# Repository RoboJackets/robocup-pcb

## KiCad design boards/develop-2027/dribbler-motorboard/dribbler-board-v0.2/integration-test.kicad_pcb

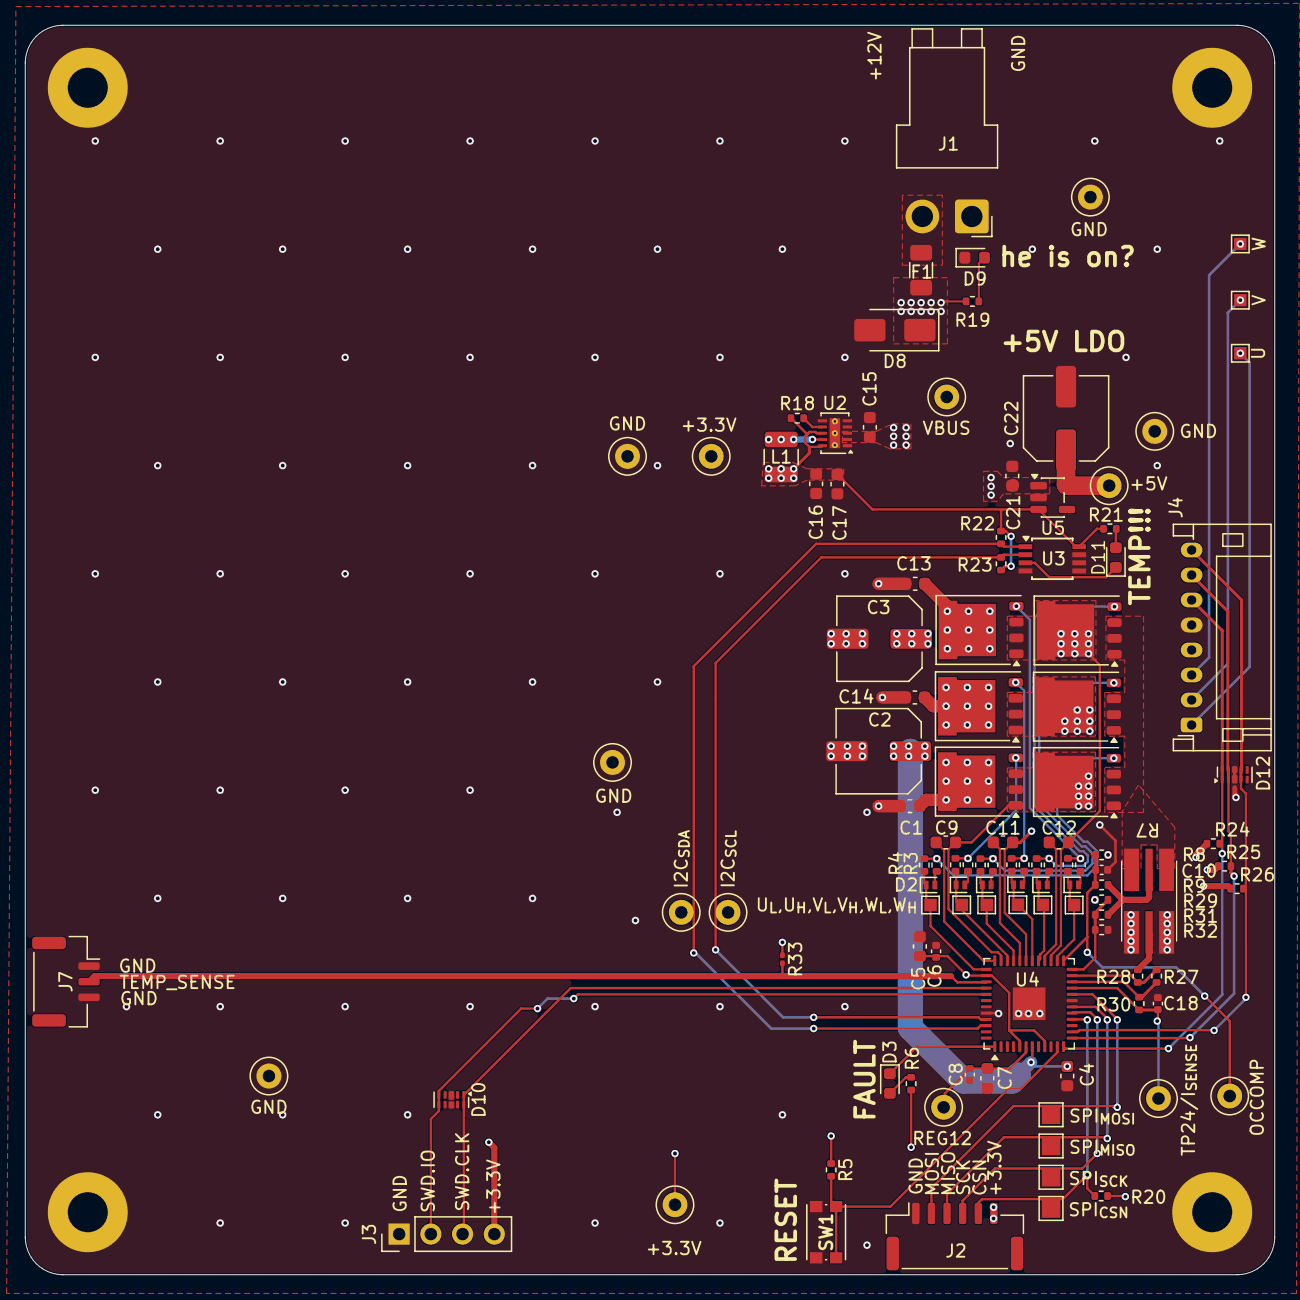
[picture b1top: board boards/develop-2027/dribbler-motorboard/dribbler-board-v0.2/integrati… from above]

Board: 4 copper layers, 100.0 x 100.0 mm, 114 parts (0 on the bottom side), 58 nets.

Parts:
+3.3V: 3.3V REG; TestPoint_Loop_D1.80mm_Drill1.0mm_Beaded
+3.3V#2: +5V EXT; TestPoint_Loop_D1.80mm_Drill1.0mm_Beaded
+5V: +5V; TestPoint_Loop_D1.80mm_Drill1.0mm_Beaded
C1, C4, C5, C9, C11, C12, C13, C14, C15, C21: 1u 63V; C_0603_1608Metric
C2, C3, C22: 100u 35V; C_Elec_6.3x5.8
C6, C8, C18: 100n 25V; C_0402_1005Metric
C7, C16, C17: 10u 25V; C_0603_1608Metric
C10: 33nF; C_0402_1005Metric
D1, D2, D4, D5, D6, D7: 1N4148WL2-TP; D_SOD-882
D3: FAULT; LED_0603_1608Metric
D8: SMAJ16A; D_SMA
D9: +12V; LED_0603_1608Metric
D10, D12: PUSB3FR4Z; Diodes_UDFN-10_1x2.5mm_P0.5mm
D11: OVERTEMP; LED_0603_1608Metric
F1: 12A; Fuse_1206_3216Metric
GND: GND; TestPoint_Loop_D1.80mm_Drill1.0mm_Beaded
GND#2, GND#4, GND#5: GND; TestPoint_Loop_D1.80mm_Drill1.0mm_Beaded
GND#3: GND EXT; TestPoint_Loop_D1.80mm_Drill1.0mm_Beaded
H1, H2, H3, H4: Corner; MountingHole_3.2mm_M3_Pad
I2C_{SCL}: SCL; TestPoint_Loop_D1.80mm_Drill1.0mm_Beaded
I2C_{SDA}: SDA; TestPoint_Loop_D1.80mm_Drill1.0mm_Beaded
J1: PWR_IN; JST_VH_B2PS-VH_1x02_P3.96mm_Horizontal
J2: COMM SPI; JST_GH_SM06B-GHS-TB_1x06-1MP_P1.25mm_Horizontal
J3: SWD Debug; PinHeader_1x04_P2.54mm_Vertical
J4: MOTOR PHASE; JST_PH_S8B-PH-K_1x08_P2.00mm_Horizontal
J7: Conn_01x03; JST_GH_SM03B-GHS-TB_1x03-1MP_P1.25mm_Horizontal
L1: 10u 540mA; L_1210_3225Metric
OCCOMP: OCCOMP; TestPoint_Loop_D1.80mm_Drill1.0mm_Beaded
Q1, Q2, Q3, Q4, Q5, Q6: STL90N10F7; PQFN-8-EP_6x5mm_P1.27mm_Generic
R1, R3, R10, R12, R14, R16: 0R; R_0402_1005Metric
R2, R4, R11, R13, R15, R17: 68R; R_0402_1005Metric
R5, R19, R20, R24, R25, R26: 10k; R_0402_1005Metric
R6, R21, R22, R23: 4.7k; R_0402_1005Metric
R7: 15m ±1% 3W; R_Shunt_Analog_2512_6332_HighAccuracy
R8: 1.13k ±0.1%; R_0402_1005Metric
R9: 33 ±0.1%; R_0402_1005Metric
R18: 100k; R_0402_1005Metric
R27: 120k ±0.1%; R_0402_1005Metric
R28, R31: 30k ±0.1%; R_0402_1005Metric
R29, R32: 240k ±0.1%; R_0402_1005Metric
R30: 300R ±1%; R_0402_1005Metric
R33: 10k; R_0201_0603Metric
REG12: REG12; TestPoint_Loop_D1.80mm_Drill1.0mm_Beaded
SPI_{CSN}: CSN; TestPoint_Pad_1.5x1.5mm
SPI_{MISO}: MISO; TestPoint_Pad_1.5x1.5mm
SPI_{MOSI}: MOSI; TestPoint_Pad_1.5x1.5mm
SPI_{SCK}: SCK; TestPoint_Pad_1.5x1.5mm
SW1: RESET; SW_Push_1P1T_NO_CK_KMR2
TP4: HSU; TestPoint_Pad_1.0x1.0mm
TP6: HSV; TestPoint_Pad_1.0x1.0mm
TP7: LSV; TestPoint_Pad_1.0x1.0mm
TP8: HSW; TestPoint_Pad_1.0x1.0mm
TP9: LSW; TestPoint_Pad_1.0x1.0mm
TP24/I_{SENSE}: ISENSEx; TestPoint_Loop_D1.80mm_Drill1.0mm_Beaded
U: OUT_{x}; TestPoint_Pad_1.0x1.0mm
U2: TPS62177DQC; WSON-10-1EP_2x3mm_P0.5mm_EP0.84x2.4mm_ThermalVias
U3: LM75ADP; TSSOP-8_3x3mm_P0.65mm
U4: STSPIN32G0B2; VQFN-48-1EP_7x7mm_P0.5mm_EP2.6x2.6mm
U5: LDI559-05EN; SOT-23-5
U_{L},U_{H},V_{L},V_{H},W_{L},W_{H}: LSU; TestPoint_Pad_1.0x1.0mm
V: OUT_{x}; TestPoint_Pad_1.0x1.0mm
VBUS: VBUS; TestPoint_Loop_D1.80mm_Drill1.0mm_Beaded
W: OUT_{x}; TestPoint_Pad_1.0x1.0mm

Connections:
+3.3V: +3.3V.1 (1_1), +3.3V#2.1 (1_1), C5.1, C6.1, C16.1, C17.1, J2.6, J3.4, L1.2, R5.1, R6.1, R8.2, R18.1, R20.1, R21.1, R22.1, R23.1, R24.1, R25.1, R26.1, R29.1, R33.1, U2.8 (~SLEEP), U2.10 (VOS), U3.8 (VCC), U4.5 (VDD), U4.9 (REG3V3), U4.38 (~STBY), U5.3 (EN)
+5V: +5V.1 (1_1), C22.1, J4.4 (+5V), U5.5 (VOUT)
/External Connections/SPI.CSN: J2.5, R20.2, SPI_{CSN}.1 (1_1), U4.16 (PA4/SPI1_~SS)
/External Connections/SPI.MISO: J2.3, SPI_{MISO}.1 (1_1), U4.18 (PA6/SPI1_MISO)
/External Connections/SPI.MOSI: J2.2, SPI_{MOSI}.1 (1_1), U4.20 (PA7/SPI1_MOSI)
/External Connections/SPI.SCK: J2.4, SPI_{SCK}.1 (1_1), U4.17 (PA5/SPI1_SCK)
/MOSFET Temperature Sensor/I2C.SCL: I2C_{SCL}.1 (1_1), R23.2, U3.2 (SCL), U4.45 (PB6/I2C1_SCL)
/MOSFET Temperature Sensor/I2C.SDA: I2C_{SDA}.1 (1_1), R22.2, U3.1 (SDA), U4.46 (PB7/I2C1_SDA)
/Motor Connections/HALL.A: D12.1 (CH1), D12.10 (CH1), J4.6 (HALL_A), R24.2, U4.12 (PA0/TIM2_CH1)
/Motor Connections/HALL.B: D12.2 (CH2), D12.9 (CH2), J4.7 (HALL_B), R25.2, U4.13 (PA1/TIM2_CH2)
/Motor Connections/HALL.C: D12.4 (CH3), D12.7 (CH3), J4.8 (HALL_C), R26.2, U4.14 (PA2/TIM2_CH3)
/Motor Connections/MOTORU: C9.2, J4.1 (PHASE_U), Q1.1 (S), Q1.2 (S), Q1.3 (S), Q2.5 (D), U.1 (1_1), U4.35 (OUTU)
/Motor Connections/MOTORV: C11.2, J4.2 (PHASE_V), Q3.1 (S), Q3.2 (S), Q3.3 (S), Q4.5 (D), U4.31 (OUTV), V.1 (1_1)
/Motor Connections/MOTORW: C12.2, J4.3 (PHASE_W), Q5.1 (S), Q5.2 (S), Q5.3 (S), Q6.5 (D), U4.27 (OUTW), W.1 (1_1)
/Motor Controller/Current Sensing/OPxN: R27.1, R28.2, U4.23 (OP1N)
/Motor Controller/Current Sensing/OPxO: R27.2, R30.1, U4.22 (OP1O)
/Motor Controller/Current Sensing/OPxP: R29.2, R31.2, R32.1, U4.24 (OP1P)
/Motor Controller/FAULT: D3.1 (K), U4.1 (PC13)
/Motor Controller/I_{SENSE}: C18.1, R30.2, TP24/I_{SENSE}.1 (1_1), U4.21 (PB1/ADC_IN)
/Motor Controller/Motor Phase U/HSx: D1.1 (K), R2.1, TP4.1 (1_1), U4.34 (HSU)
/Motor Controller/Motor Phase U/LSx: D2.1 (K), R4.1, U4.37 (LSU), U_{L},U_{H},V_{L},V_{H},W_{L},W_{H}.1 (1_1)
/Motor Controller/Motor Phase V/HSx: D4.1 (K), R11.1, TP6.1 (1_1), U4.30 (HSV)
/Motor Controller/Motor Phase V/LSx: D5.1 (K), R13.1, TP7.1 (1_1), U4.33 (LSV)
/Motor Controller/Motor Phase W/HSx: D6.1 (K), R15.1, TP8.1 (1_1), U4.26 (HSW)
/Motor Controller/Motor Phase W/LSx: D7.1 (K), R17.1, TP9.1 (1_1), U4.29 (LSW)
/Motor Controller/SHUNTN: R7.3, R28.1
/Motor Controller/SHUNTP: R7.2, R9.1, R31.1
/Motor Controller/SHUNT_H: Q2.1 (S), Q2.2 (S), Q2.3 (S), Q4.1 (S), Q4.2 (S), Q4.3 (S), Q6.1 (S), Q6.2 (S), Q6.3 (S), R7.1
/Motor Controller/SWD.CLK: D10.1 (CH1), D10.10 (CH1), J3.3, U4.40 (PA13/SWCLK)
/Motor Controller/SWD.IO: D10.5 (CH5), D10.6 (CH5), J3.2, U4.41 (PA14/SWDIO/BOOT0)
/Motor Controller/TEMP_SENSE: J7.2, R33.2, U4.39 (PA12[PA10]/SPI2_MOSI)
/Motor Controller/~RST: R5.2, SW1.2 (B), U4.11 (PF2/~RST)
GND: C1.2, C2.2, C3.2, C4.2, C5.2, C6.2, C7.2, C8.2, C10.2, C13.2, C14.2, C15.2, C16.2, C17.2, C18.2, C21.1, C22.2, D8.2 (A2), D9.1 (K), D10.3 (GND), D10.8 (GND), D12.3 (GND), D12.8 (GND), GND.1 (1_1), GND#2.1 (1_1), GND#3.1 (1_1), GND#4.1 (1_1), GND#5.1 (1_1), H1.1 (1_1), H2.1 (1_1), H3.1 (1_1), H4.1 (1_1), J1.1, J2.1, J3.1, J4.5 (GND), J7.1, J7.3, R7.4, R32.2, SW1.1 (A), U2.1 (PGND), U2.4 (NC), U2.5 (FB), U2.6 (AGND), U2.11 (PAD), U3.4 (GND), U3.5 (A2), U3.6 (A1), U3.7 (A0), U4.19 (TESTMODE), U4.44 (GND), U4.49 (EPAD), U5.2 (GND)
unnamed: D1.2 (A), R1.1
unnamed: D2.2 (A), R3.1
unnamed: D3.2 (A), R6.2
unnamed: D4.2 (A), R10.1
unnamed: D5.2 (A), R12.1
unnamed: D6.2 (A), R14.1
unnamed: D7.2 (A), R16.1
unnamed: D9.2 (A), R19.2
unnamed: D11.2 (A), R21.2
unnamed: D11.1 (K), U3.3 (OS)
unnamed: F1.1, J1.2
unnamed: Q1.4 (G), R1.2, R2.2
unnamed: Q2.4 (G), R3.2, R4.2
unnamed: Q3.4 (G), R10.2, R11.2
unnamed: Q4.4 (G), R12.2, R13.2
unnamed: Q5.4 (G), R14.2, R15.2
unnamed: Q6.4 (G), R16.2, R17.2
unnamed: R18.2, U2.7 (PG)
unnamed: L1.1, U2.9 (SW)
unnamed: C7.1, C8.1, REG12.1 (1_1), U4.6 (REG12)
unnamed: C9.1, U4.36 (VBOOTU)
unnamed: C11.1, U4.32 (VBOOTV)
unnamed: C12.1, U4.28 (VBOOTW)
unnamed: C10.1, OCCOMP.1 (1_1), R8.1, R9.2, U4.25 (OCCOMP)
VBUS: C1.1, C2.1, C3.1, C4.1, C13.1, C14.1, C15.1, C21.2, D8.1 (A1), F1.2, Q1.5 (D), Q3.5 (D), Q5.5 (D), R19.1, U2.2 (VIN), U2.3 (EN), U4.7 (VM), U5.1 (VIN), VBUS.1 (1_1)

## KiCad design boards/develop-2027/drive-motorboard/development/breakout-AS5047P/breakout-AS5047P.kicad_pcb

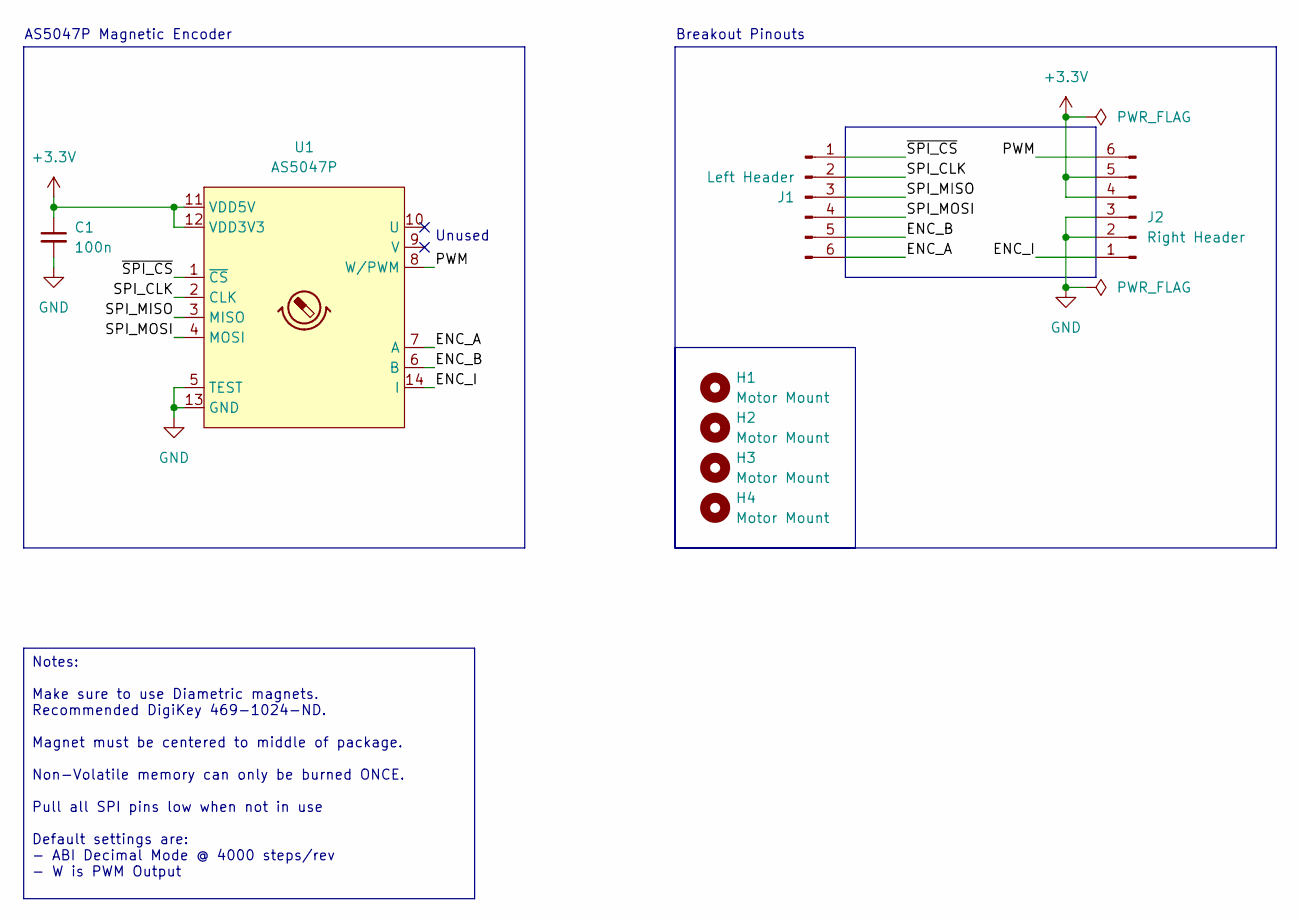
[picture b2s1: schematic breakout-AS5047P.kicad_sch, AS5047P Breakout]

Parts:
C1: 100n; C_0603_1608Metric_Pad1.08x0.95mm_HandSolder
H1, H2, H3, H4: Motor Mount; MountingHole_3.2mm_M3_Pad
J1: Left Header; PinHeader_1x06_P2.54mm_Vertical
J2: Right Header; PinHeader_1x06_P2.54mm_Vertical
U1: AS5047P; TSSOP-14_4.4x5mm_P0.65mm; Manufacturer P/N AS5047P

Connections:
+3.3V: C1.1, J2.4, J2.5, U1.11 (VDD5V), U1.12 (VDD3V3)
/ENC_A: J1.6, U1.7 (A)
/ENC_B: J1.5, U1.6 (B)
/ENC_I: J2.1, U1.14 (I)
/PWM: J2.6, U1.8 (W/PWM)
/SPI_CLK: J1.2, U1.2 (CLK)
/SPI_MISO: J1.3, U1.3 (MISO)
/SPI_MOSI: J1.4, U1.4 (MOSI)
/~SPI_CS: J1.1, U1.1 (~CS)
GND: C1.2, J2.2, J2.3, U1.5 (TEST), U1.13 (GND)

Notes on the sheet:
AS5047P Magnetic Encoder
Unused
Breakout Pinouts
Notes: Make sure to use Diametric magnets. Recommended DigiKey 469-1024-ND. Magnet must be centered to middle of package. Non-Volatile memory can only be burned ONCE. Pull all SPI pins low when not in use Default settings are: - ABI Decimal Mode @ 4000 steps/rev - W is PWM Output

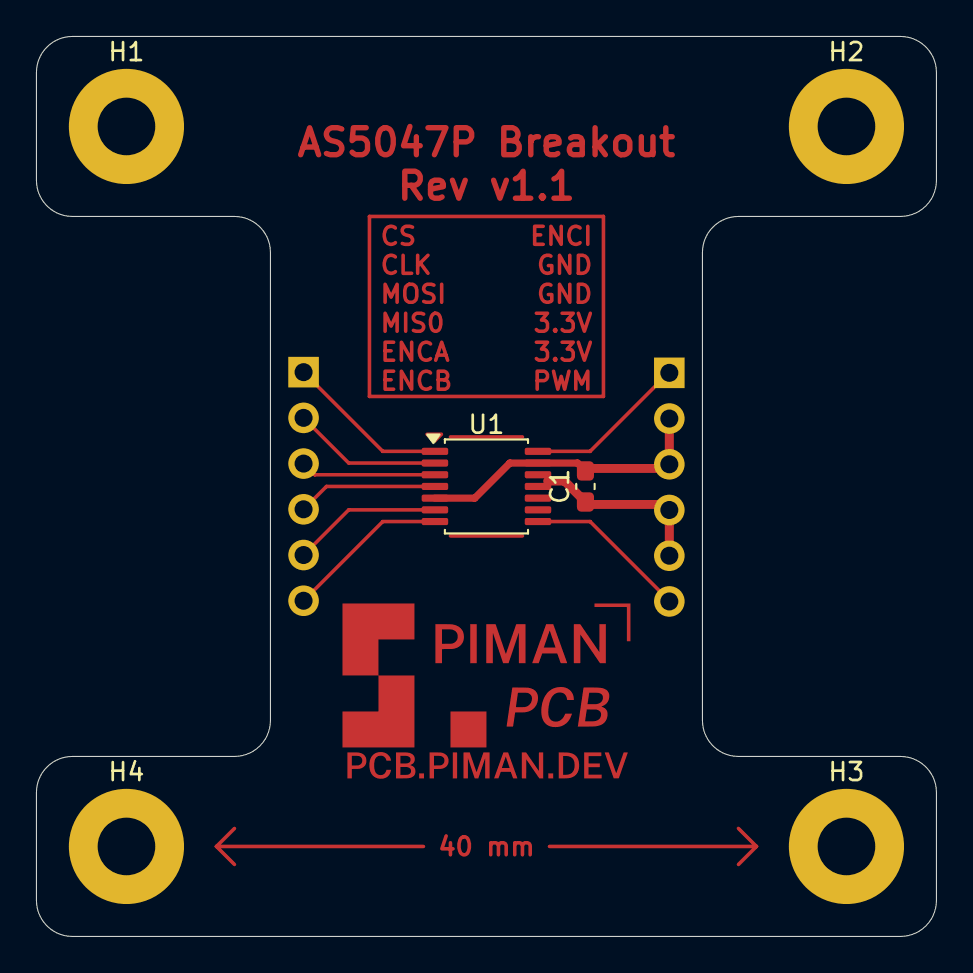
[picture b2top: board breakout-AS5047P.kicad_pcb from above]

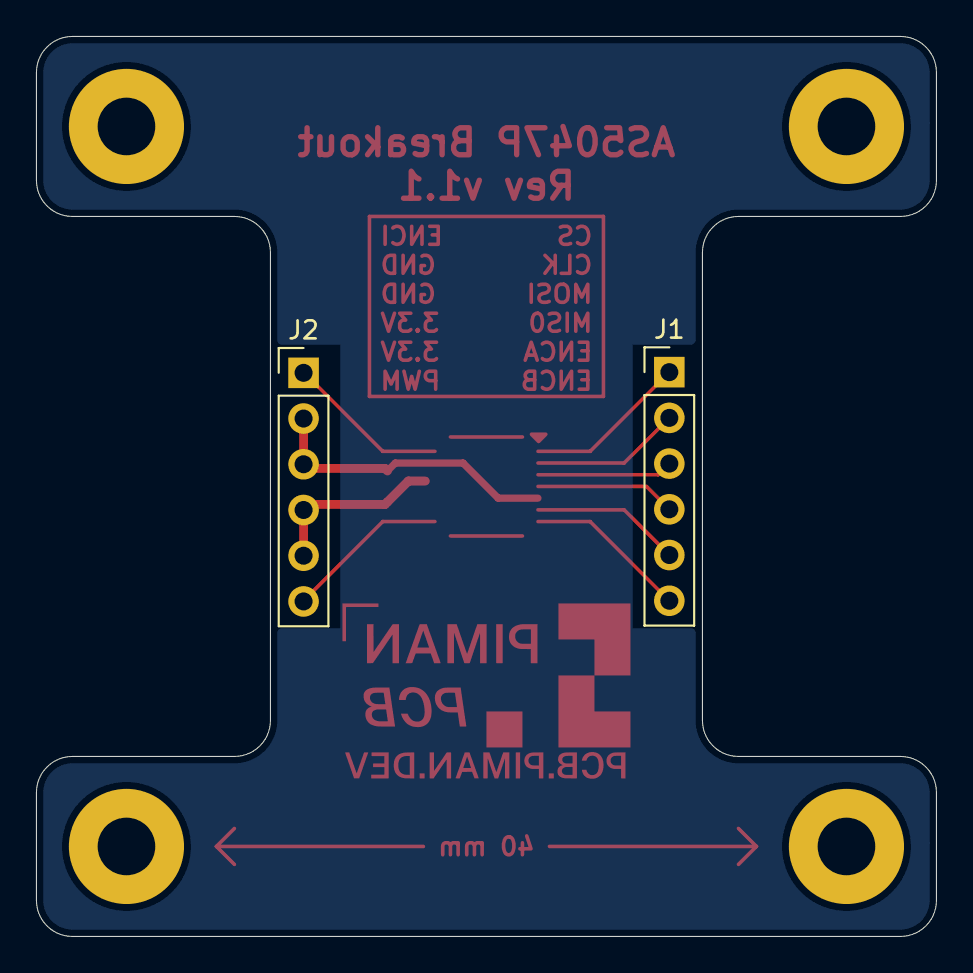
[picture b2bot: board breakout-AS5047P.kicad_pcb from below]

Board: 2 copper layers, 50.0 x 50.0 mm, 8 parts (2 on the bottom side), 10 nets.

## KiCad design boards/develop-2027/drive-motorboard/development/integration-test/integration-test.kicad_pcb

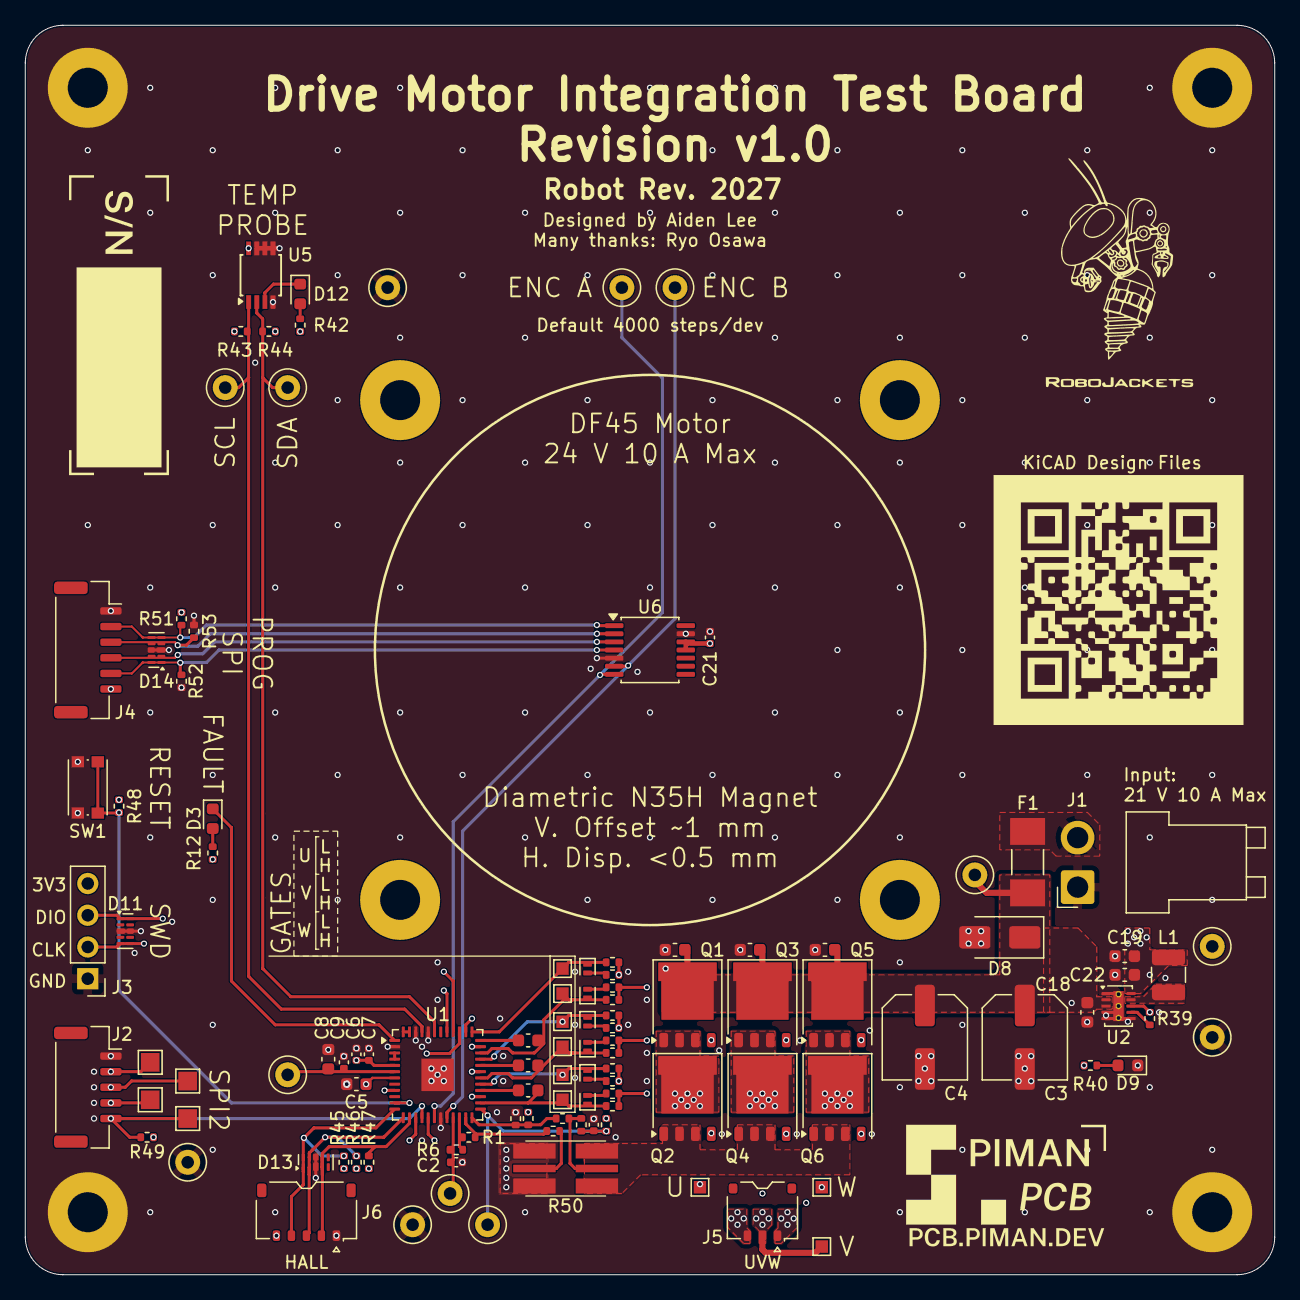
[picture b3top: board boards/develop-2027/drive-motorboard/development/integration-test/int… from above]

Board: 6 copper layers, 100.0 x 100.0 mm, 120 parts (0 on the bottom side), 64 nets.

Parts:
C1, C5, C10, C12, C13, C14, C15, C18: 1u 63V; C_0603_1608Metric
C2, C21: 100n; C_0402_1005Metric
C3, C4: 100u 35V; C_Elec_6.3x5.8
C6: 1u 10V; C_0402_1005Metric
C7: 100n 10V; C_0402_1005Metric
C8, C19, C22: 10u 25V; C_0603_1608Metric
C9: 100n 25V; C_0402_1005Metric
C11: 1n; C_0402_1005Metric
D1, D2, D4, D5, D6, D7: 1N4148WL2-TP; D_SOD-882
D3: FAULT; LED_0603_1608Metric
D8: SMAJ22A; D_SMA
D9: VBATT PWR; LED_0603_1608Metric
D11, D13, D14: PUSB3FR4Z; Diodes_UDFN-10_1x2.5mm_P0.5mm
D12: OVERTEMP; LED_0603_1608Metric
F1: 10A 60V; Fuse_2410_6125Metric
H1, H2, H3, H4: Corner; MountingHole_3.2mm_M3_Pad
H5, H6, H7, H8: Motor Mount; MountingHole_3.2mm_M3_Pad
J1: PWR_IN; JST_VH_B2PS-VH_1x02_P3.96mm_Horizontal
J2: COMM SPI; JST_GH_SM05B-GHS-TB_1x05-1MP_P1.25mm_Horizontal
J3: SWD Debug; PinHeader_1x04_P2.54mm_Vertical
J4: PROG SPI; JST_GH_SM06B-GHS-TB_1x06-1MP_P1.25mm_Horizontal
J5: MOTOR UVW; JST_ACH_BM03B-ACHSS-GAN-ETF_1x03-1MP_P1.20mm_Vertical
J6: MOTOR HALL; JST_ACH_BM05B-ACHSS-A-GAN-ETF_1x05-1MP_P1.20mm_Vertical
L1: 10u 540mA; L_1210_3225Metric
Q1, Q2, Q3, Q4, Q5, Q6: STL90N10F7; PQFN-8-EP_6x5mm_P1.27mm_Generic
R1: 8.25k ±0.1%; R_0402_1005Metric
R2, R8, R18, R19, R22, R23: 0R; R_0402_1005Metric
R3, R7, R15: 1.13k ±0.1%; R_0402_1005Metric
R4, R10, R11, R17, R20, R21: 68R; R_0402_1005Metric
R5, R9: 16.5k ±0.1%; R_0402_1005Metric
R6: 300R ±1%; R_0402_1005Metric
R12, R42, R43, R44, R51, R52, R53: 4.7k; R_0402_1005Metric
R14: 33k ±0.1%; R_0402_1005Metric
R39: 100k; R_0402_1005Metric
R40, R45, R46, R47, R48, R49: 10k; R_0402_1005Metric
R50: 15m ±1% 3W; R_Shunt_Analog_2512_6332_HighAccuracy
SW1: RESET; SW_Push_1P1T_NO_CK_KMR2
TP1: ISENSEx; TestPoint_Loop_D1.80mm_Drill1.0mm_Beaded
TP6: REG12; TestPoint_Loop_D1.80mm_Drill1.0mm_Beaded
TP7: OCCOMP; TestPoint_Loop_D1.80mm_Drill1.0mm_Beaded
TP8: HSU; TestPoint_Pad_1.0x1.0mm
TP9: LSU; TestPoint_Pad_1.0x1.0mm
TP10: HSV; TestPoint_Pad_1.0x1.0mm
TP11: LSV; TestPoint_Pad_1.0x1.0mm
TP12: HSW; TestPoint_Pad_1.0x1.0mm
TP13: LSW; TestPoint_Pad_1.0x1.0mm
TP14, TP15, TP16: OUT_{x}; TestPoint_Pad_1.0x1.0mm
TP20: 3.3V REG; TestPoint_Loop_D1.80mm_Drill1.0mm_Beaded
TP21: VBUS; TestPoint_Loop_D1.80mm_Drill1.0mm_Beaded
TP22, TP23, TP24, TP25: GND; TestPoint_Loop_D1.80mm_Drill1.0mm_Beaded
TP27: CSN; TestPoint_Pad_1.5x1.5mm
TP28: SCK; TestPoint_Pad_1.5x1.5mm
TP29: MISO; TestPoint_Pad_1.5x1.5mm
TP30: MOSI; TestPoint_Pad_1.5x1.5mm
TP31: SDA; TestPoint_Loop_D1.80mm_Drill1.0mm_Beaded
TP32: SCL; TestPoint_Loop_D1.80mm_Drill1.0mm_Beaded
TP33: ENC A; TestPoint_Loop_D1.80mm_Drill1.0mm_Beaded
TP34: ENC B; TestPoint_Loop_D1.80mm_Drill1.0mm_Beaded
U1: STSPIN32G0A2; VQFN-48-1EP_7x7mm_P0.5mm_EP2.6x2.6mm
U2: TPS62177DQC; WSON-10-1EP_2x3mm_P0.5mm_EP0.84x2.4mm_ThermalVias
U5: LM75ADP; TSSOP-8_3x3mm_P0.65mm
U6: AS5047P; TSSOP-14_4.4x5mm_P0.65mm

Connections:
+3.3V: C6.1, C7.1, C19.1, C21.1, C22.1, J3.4, J4.6, J6.5, L1.2, R5.1, R12.1, R14.2, R39.1, R42.1, R43.1, R44.1, R45.1, R46.1, R47.1, R48.1, R49.1, R51.1, TP20.1 (1_1), U1.5 (VDD), U1.9 (REG3V3), U1.38 (~STBY), U2.8 (~SLEEP), U2.10 (VOS), U5.8 (VCC), U6.11 (VDD5V), U6.12 (VDD3V3)
/External Connections/SPI.CSN: J2.5, R49.2, TP27.1 (1_1), U1.16 (PA4/SPI2_~SS)
/External Connections/SPI.MISO: J2.3, TP29.1 (1_1), U1.15 (PA3/SPI2_MISO)
/External Connections/SPI.MOSI: J2.2, TP30.1 (1_1), U1.39 (PA12[PA10]/SPI2_MOSI)
/External Connections/SPI.SCK: J2.4, TP28.1 (1_1), U1.17 (PA5/SPI2_SCK)
/Magnetic Encoder/ENC.A: TP33.1 (1_1), U1.18 (PA6/TIM3_CH1), U6.7 (A)
/Magnetic Encoder/ENC.B: TP34.1 (1_1), U1.20 (PA7/TIM3_CH2), U6.6 (B)
/Magnetic Encoder/PROGSPI.CLK: D14.4 (CH3), D14.7 (CH3), J4.3, R53.1, U6.2 (CLK)
/Magnetic Encoder/PROGSPI.CSN: D14.5 (CH5), D14.6 (CH5), J4.2, R51.2, U6.1 (~CS)
/Magnetic Encoder/PROGSPI.MISO: D14.2 (CH2), D14.9 (CH2), J4.4, U6.3 (MISO)
/Magnetic Encoder/PROGSPI.MOSI: D14.1 (CH1), D14.10 (CH1), J4.5, R52.1, U6.4 (MOSI)
/Motor Connections/HALL.A: D13.1 (CH1), D13.10 (CH1), J6.4, R45.2, U1.12 (PA0/TIM2_CH1)
/Motor Connections/HALL.B: D13.2 (CH2), D13.9 (CH2), J6.3, R46.2, U1.13 (PA1/TIM2_CH2)
/Motor Connections/HALL.C: D13.4 (CH3), D13.7 (CH3), J6.2, R47.2, U1.14 (PA2/TIM2_CH3)
/Motor Connections/MOTORU: J5.3, Q1.1 (S), Q1.2 (S), Q1.3 (S), Q2.5 (D), TP14.1 (1_1), U1.35 (OUTU)
/Motor Connections/MOTORV: J5.2, Q3.1 (S), Q3.2 (S), Q3.3 (S), Q4.5 (D), TP15.1 (1_1), U1.31 (OUTV)
/Motor Connections/MOTORW: J5.1, Q5.1 (S), Q5.2 (S), Q5.3 (S), Q6.5 (D), TP16.1 (1_1), U1.27 (OUTW)
/Motor Controller/Current Sensing/OPxN: R1.1, R3.2, U1.23 (OP1N)
/Motor Controller/Current Sensing/OPxO: R1.2, R6.1, U1.22 (OP1O)
/Motor Controller/Current Sensing/OPxP: R5.2, R7.2, R9.1, U1.24 (OP1P)
/Motor Controller/FAULT: D3.1 (K), U1.1 (PC14)
/Motor Controller/I2C.SCL: R44.2, TP32.1 (1_1), U1.43 (PB6/I2C1_SCL), U5.2 (SCL)
/Motor Controller/I2C.SDA: R43.2, TP31.1 (1_1), U1.45 (PB7/I2C1_SDA), U5.1 (SDA)
/Motor Controller/I_{SENSE}: C2.1, R6.2, TP1.1 (1_1), U1.21 (PB1)
/Motor Controller/Motor Phase U/HSx: C10.2, D1.1 (K), R4.1, TP8.1 (1_1), U1.34 (HSU)
/Motor Controller/Motor Phase U/LSx: D2.1 (K), R10.1, TP9.1 (1_1), U1.37 (LSU)
/Motor Controller/Motor Phase V/HSx: C12.2, D4.1 (K), R11.1, TP10.1 (1_1), U1.30 (HSV)
/Motor Controller/Motor Phase V/LSx: D5.1 (K), R17.1, TP11.1 (1_1), U1.33 (LSV)
/Motor Controller/Motor Phase W/HSx: C13.2, D6.1 (K), R20.1, TP12.1 (1_1), U1.26 (HSW)
/Motor Controller/Motor Phase W/LSx: D7.1 (K), R21.1, TP13.1 (1_1), U1.29 (LSW)
/Motor Controller/SHUNTN: R3.1, R50.3
/Motor Controller/SHUNTP: R7.1, R15.1, R50.2
/Motor Controller/SHUNT_H: Q2.1 (S), Q2.2 (S), Q2.3 (S), Q4.1 (S), Q4.2 (S), Q4.3 (S), Q6.1 (S), Q6.2 (S), Q6.3 (S), R50.1
/Motor Controller/SWD.CLK: D11.5 (CH5), D11.6 (CH5), J3.2, U1.41 (PA14/SWDCLK/BOOT0)
/Motor Controller/SWD.IO: D11.1 (CH1), D11.10 (CH1), J3.3, U1.40 (PA13/SWDIO)
/Motor Controller/~RST: R48.2, SW1.2 (B), U1.11 (PF2/~RST)
GND: C1.2, C2.2, C3.2, C4.2, C5.2, C6.2, C7.2, C8.2, C9.2, C11.2, C14.2, C15.2, C18.2, C19.2, C21.2, C22.2, D8.2 (A2), D9.1 (K), D11.3 (GND), D11.8 (GND), D13.3 (GND), D13.8 (GND), D14.3 (GND), D14.8 (GND), H1.1 (1_1), H2.1 (1_1), H3.1 (1_1), H4.1 (1_1), J1.1, J2.1, J3.1, J4.1, J6.1, R9.2, R50.4, R52.2, R53.2, SW1.1 (A), TP22.1 (1_1), TP23.1 (1_1), TP24.1 (1_1), TP25.1 (1_1), U1.2 (OP2P), U1.19 (TESTMODE), U1.44 (GND), U1.46 (OP3P), U1.49 (EPAD), U2.1 (PGND), U2.4 (NC), U2.5 (FB), U2.6 (AGND), U2.11 (PAD), U5.4 (GND), U5.5 (A2), U5.6 (A1), U5.7 (A0), U6.5 (TEST), U6.13 (GND)
unnamed: D1.2 (A), R2.1
unnamed: D2.2 (A), R8.1
unnamed: D3.2 (A), R12.2
unnamed: D4.2 (A), R18.1
unnamed: D5.2 (A), R19.1
unnamed: D6.2 (A), R22.1
unnamed: D7.2 (A), R23.1
unnamed: D9.2 (A), R40.2
unnamed: D12.2 (A), R42.2
unnamed: D12.1 (K), U5.3 (OS)
unnamed: F1.1, J1.2
unnamed: Q1.4 (G), R2.2, R4.2
unnamed: Q2.4 (G), R8.2, R10.2
unnamed: Q3.4 (G), R11.2, R18.2
unnamed: Q4.4 (G), R17.2, R19.2
unnamed: Q5.4 (G), R20.2, R22.2
unnamed: Q6.4 (G), R21.2, R23.2
unnamed: C10.1, U1.36 (VBOOTU)
unnamed: C12.1, U1.32 (VBOOTV)
unnamed: C13.1, U1.28 (VBOOTW)
unnamed: U1.3 (OP2N), U1.4 (OP2O)
unnamed: U1.47 (OP3N), U1.48 (OP3O)
unnamed: C11.1, R14.1, R15.2, TP7.1 (1_1), U1.25 (OCCOMP)
unnamed: C8.1, C9.1, TP6.1 (1_1), U1.6 (REG12)
unnamed: R39.2, U2.7 (PG)
unnamed: L1.1, U2.9 (SW)
VBUS: C1.1, C3.1, C4.1, C5.1, C14.1, C15.1, C18.1, D8.1 (A1), F1.2, Q1.5 (D), Q3.5 (D), Q5.5 (D), R40.1, TP21.1 (1_1), U1.7 (VM), U2.2 (VIN), U2.3 (EN)

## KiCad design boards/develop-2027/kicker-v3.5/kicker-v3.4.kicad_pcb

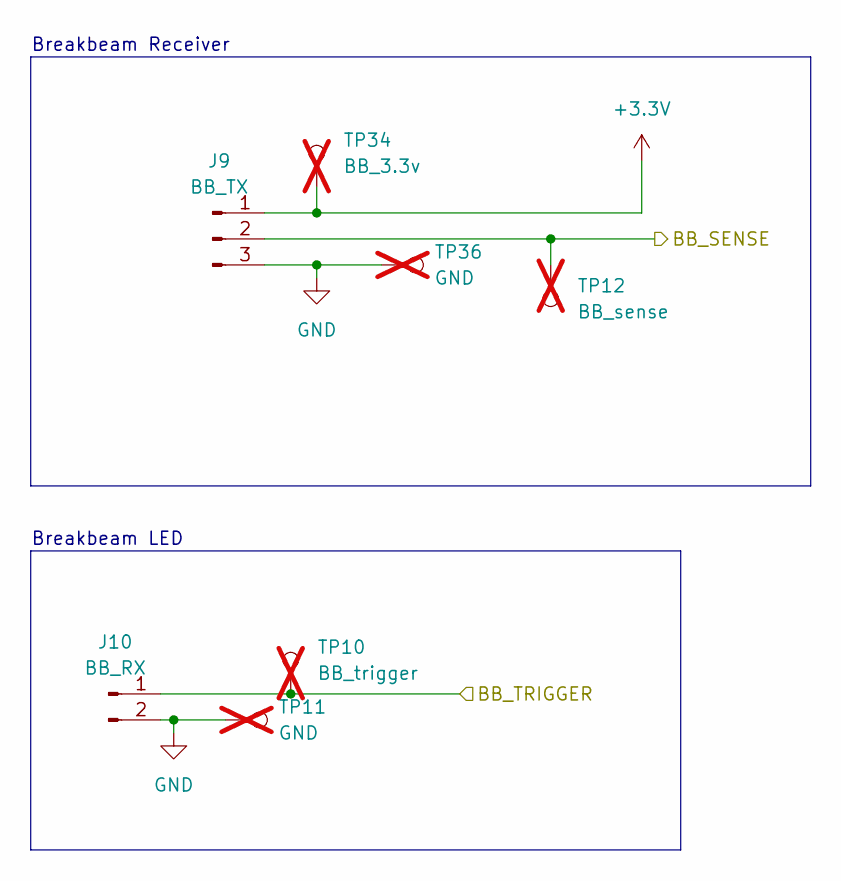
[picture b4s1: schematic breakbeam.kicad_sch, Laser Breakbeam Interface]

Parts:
J9: BB_TX; JST_PH_S3B-PH-K_1x03_P2.00mm_Horizontal; Manufacturer P/N IPCW200W13NW01R; LCSC P/N C2982156
J10: BB_RX; JST_PH_S2B-PH-K_1x02_P2.00mm_Horizontal; Manufacturer P/N IPCW200W12NW01R; LCSC P/N C2982155
TP10: BB_trigger; TestPoint_Pad_D1.0mm; not fitted
TP11, TP36: GND; TestPoint_Pad_D1.0mm; not fitted
TP12: BB_sense; TestPoint_Pad_D1.0mm; not fitted
TP34: BB_3.3v; TestPoint_Pad_D1.0mm; not fitted

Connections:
+3.3V: J9.1, TP34.1 (1_1); also elsewhere on the board
/Breakbeam/BB_SENSE: J9.2, TP12.1 (1_1); also elsewhere on the board
/Breakbeam/BB_TRIGGER: J10.1, TP10.1 (1_1); also elsewhere on the board
GND: J9.3, J10.2, TP11.1 (1_1), TP36.1 (1_1); also elsewhere on the board

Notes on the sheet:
Breakbeam LED
Breakbeam Receiver

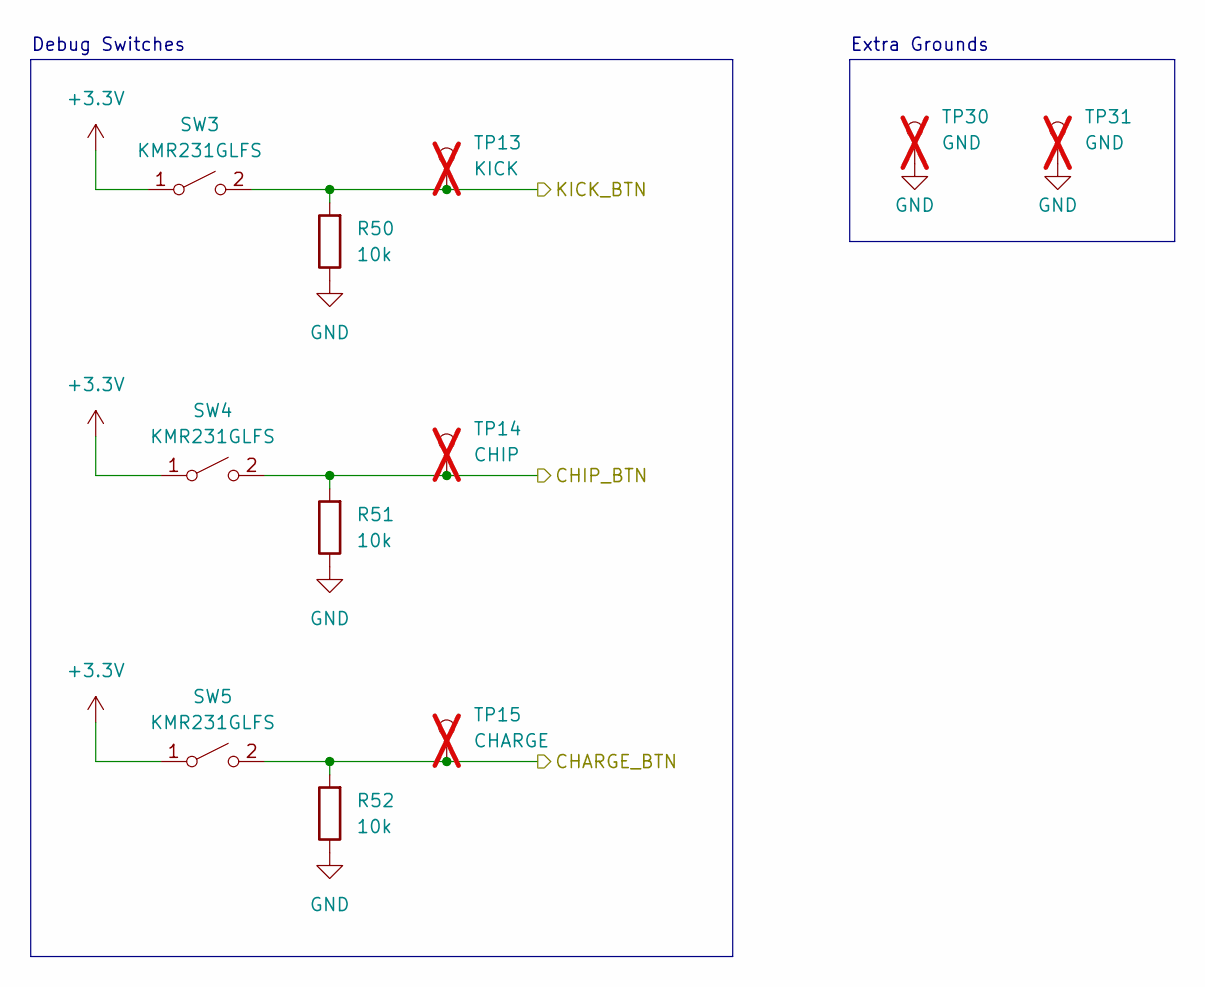
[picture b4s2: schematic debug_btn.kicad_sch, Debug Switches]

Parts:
R50, R51, R52: 10k; R_0603_1608Metric; Manufacturer P/N RC0603FR-0710KL; LCSC P/N C98220
SW3, SW4, SW5: KMR231GLFS; SW_Push_1P1T_NO_CK_KMR2; Manufacturer P/N KMR231GLFS
TP13: KICK; TestPoint_Pad_D1.0mm; not fitted
TP14: CHIP; TestPoint_Pad_D1.0mm; not fitted
TP15: CHARGE; TestPoint_Pad_D1.0mm; not fitted
TP30, TP31: GND; TestPoint_Pad_D1.0mm; not fitted

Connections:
+3.3V: SW3.1 (A), SW4.1 (A), SW5.1 (A); also elsewhere on the board
/Debug Buttons/CHARGE_BTN: R52.2, SW5.2 (B), TP15.1 (1_1); also elsewhere on the board
/Debug Buttons/CHIP_BTN: R51.2, SW4.2 (B), TP14.1 (1_1); also elsewhere on the board
/Debug Buttons/KICK_BTN: R50.2, SW3.2 (B), TP13.1 (1_1); also elsewhere on the board
GND: R50.1, R51.1, R52.1, TP30.1 (1_1), TP31.1 (1_1); also elsewhere on the board

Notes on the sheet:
Extra Grounds
Debug Switches

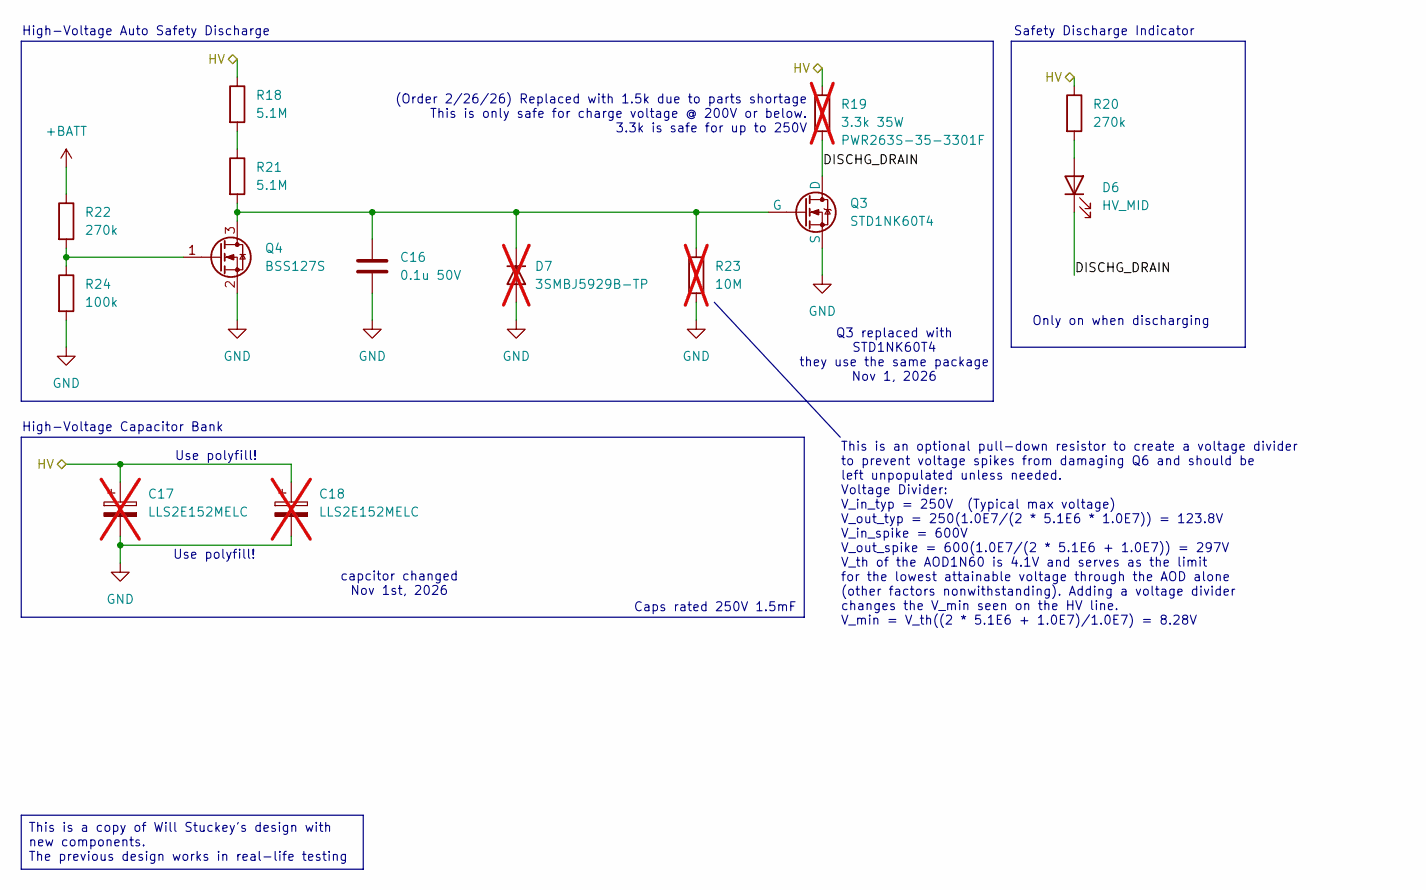
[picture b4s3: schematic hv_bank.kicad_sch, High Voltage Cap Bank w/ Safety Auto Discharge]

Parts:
C16: 0.1u 50V; C_0603_1608Metric; Manufacturer P/N CL10B104KB8NNNC; LCSC P/N C1591
C17, C18: LLS2E152MELC; CAP_C40_NCH; not fitted
D6: HV_MID; LED_0603_1608Metric; LCSC P/N C965804
D7: 3SMBJ5929B-TP; D_SMB; Manufacturer P/N 3SMBJ5929B-TP; not fitted
Q3: STD1NK60T4; TO-252-2; Manufacturer P/N STD1NK60T4; LCSC P/N C361030
Q4: BSS127S; SOT-23; Manufacturer P/N BSS127S; LCSC P/N C154890
R18, R21: 5.1M; R_1206_3216Metric; Manufacturer P/N RCT065M1FLF; LCSC P/N C185741
R19: 3.3k 35W; RES_PWR263S-35-3301F; Manufacturer P/N PWR263S-35-3301F; not fitted
R20: 270k; R_2512_6332Metric; Manufacturer P/N HP122WF2703T4E; LCSC P/N C2775917
R22: 270k; R_0603_1608Metric; Manufacturer P/N RC0603FR-07270KL; LCSC P/N C137755
R23: 10M; R_0603_1608Metric; not fitted
R24: 100k; R_0603_1608Metric; Manufacturer P/N RC0603FR-07100KL; LCSC P/N C14675

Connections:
+BATT: R22.1; also elsewhere on the board
/Capacitor Bank/DISCHG_DRAIN: D6.1 (K), Q3.2 (D), R19.2
/Capacitor Bank/HV: C17.1, C18.1, R18.1, R19.1, R20.1; also elsewhere on the board
GND: C16.2, C17.2, C18.2, D7.2 (A), Q3.3 (S), Q4.2 (S), R23.2, R24.2; also elsewhere on the board
unnamed: D6.2 (A), R20.2
unnamed: C16.1, D7.1 (K), Q3.1 (G), Q4.3 (D), R21.2, R23.1
unnamed: Q4.1 (G), R22.2, R24.1
unnamed: R18.2, R21.1

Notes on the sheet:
Safety Discharge Indicator
capcitor changed Nov 1st, 2026
Only on when discharging
High-Voltage Capacitor Bank
Use polyfill!
Caps rated 250V 1.5mF
High-Voltage Auto Safety Discharge
(Order 2/26/26) Replaced with 1.5k due to parts shortage This is only safe for charge voltage @ 200V or below. 3.3k is safe for up to 250V
Q3 replaced with STD1NK60T4 they use the same package Nov 1, 2026
This is an optional pull-down resistor to create a voltage divider to prevent voltage spikes from damaging Q6 and should be left unpopulated unless needed. Voltage Divider: V_in_typ = 250V (Typical max voltage) V_out_typ = 250(1.0E7/(2 * 5.1E6 * 1.0E7)) = 123.8V V_in_spike = 600V V_out_spike = 600(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
This is a copy of Will Stuckey's design with new components. The previous design works in real-life testing
